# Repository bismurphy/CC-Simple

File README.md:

# CC-Simple
A simple radio using the TI CC-1110 (WORK IN PROGRESS)

License & Legal Information
---------------------------

This project is directly derived from the Planet Labs OpenLST radio. My aim was to simplify it as much as possible to allow for experimentation and education.

The OpenLST is provided under a Creative Commons Attribution-ShareAlike 4.0 International License, which requires me to give them recognition, as well as to also put my work under that license. The Planet Labs repository can be found at https://github.com/OpenLST/openlst-hw

Copyright 2018 Planet Labs Inc. This work is licensed under a
Creative Commons Attribution-ShareAlike 4.0 International License.

This document may contain technology or software the export of which
is or may be restricted by the Export Administration Act and the
Export Administration Regulations (EAR), 15 C.F.R. parts
730-774. Diversion contrary to U.S. law is prohibited.

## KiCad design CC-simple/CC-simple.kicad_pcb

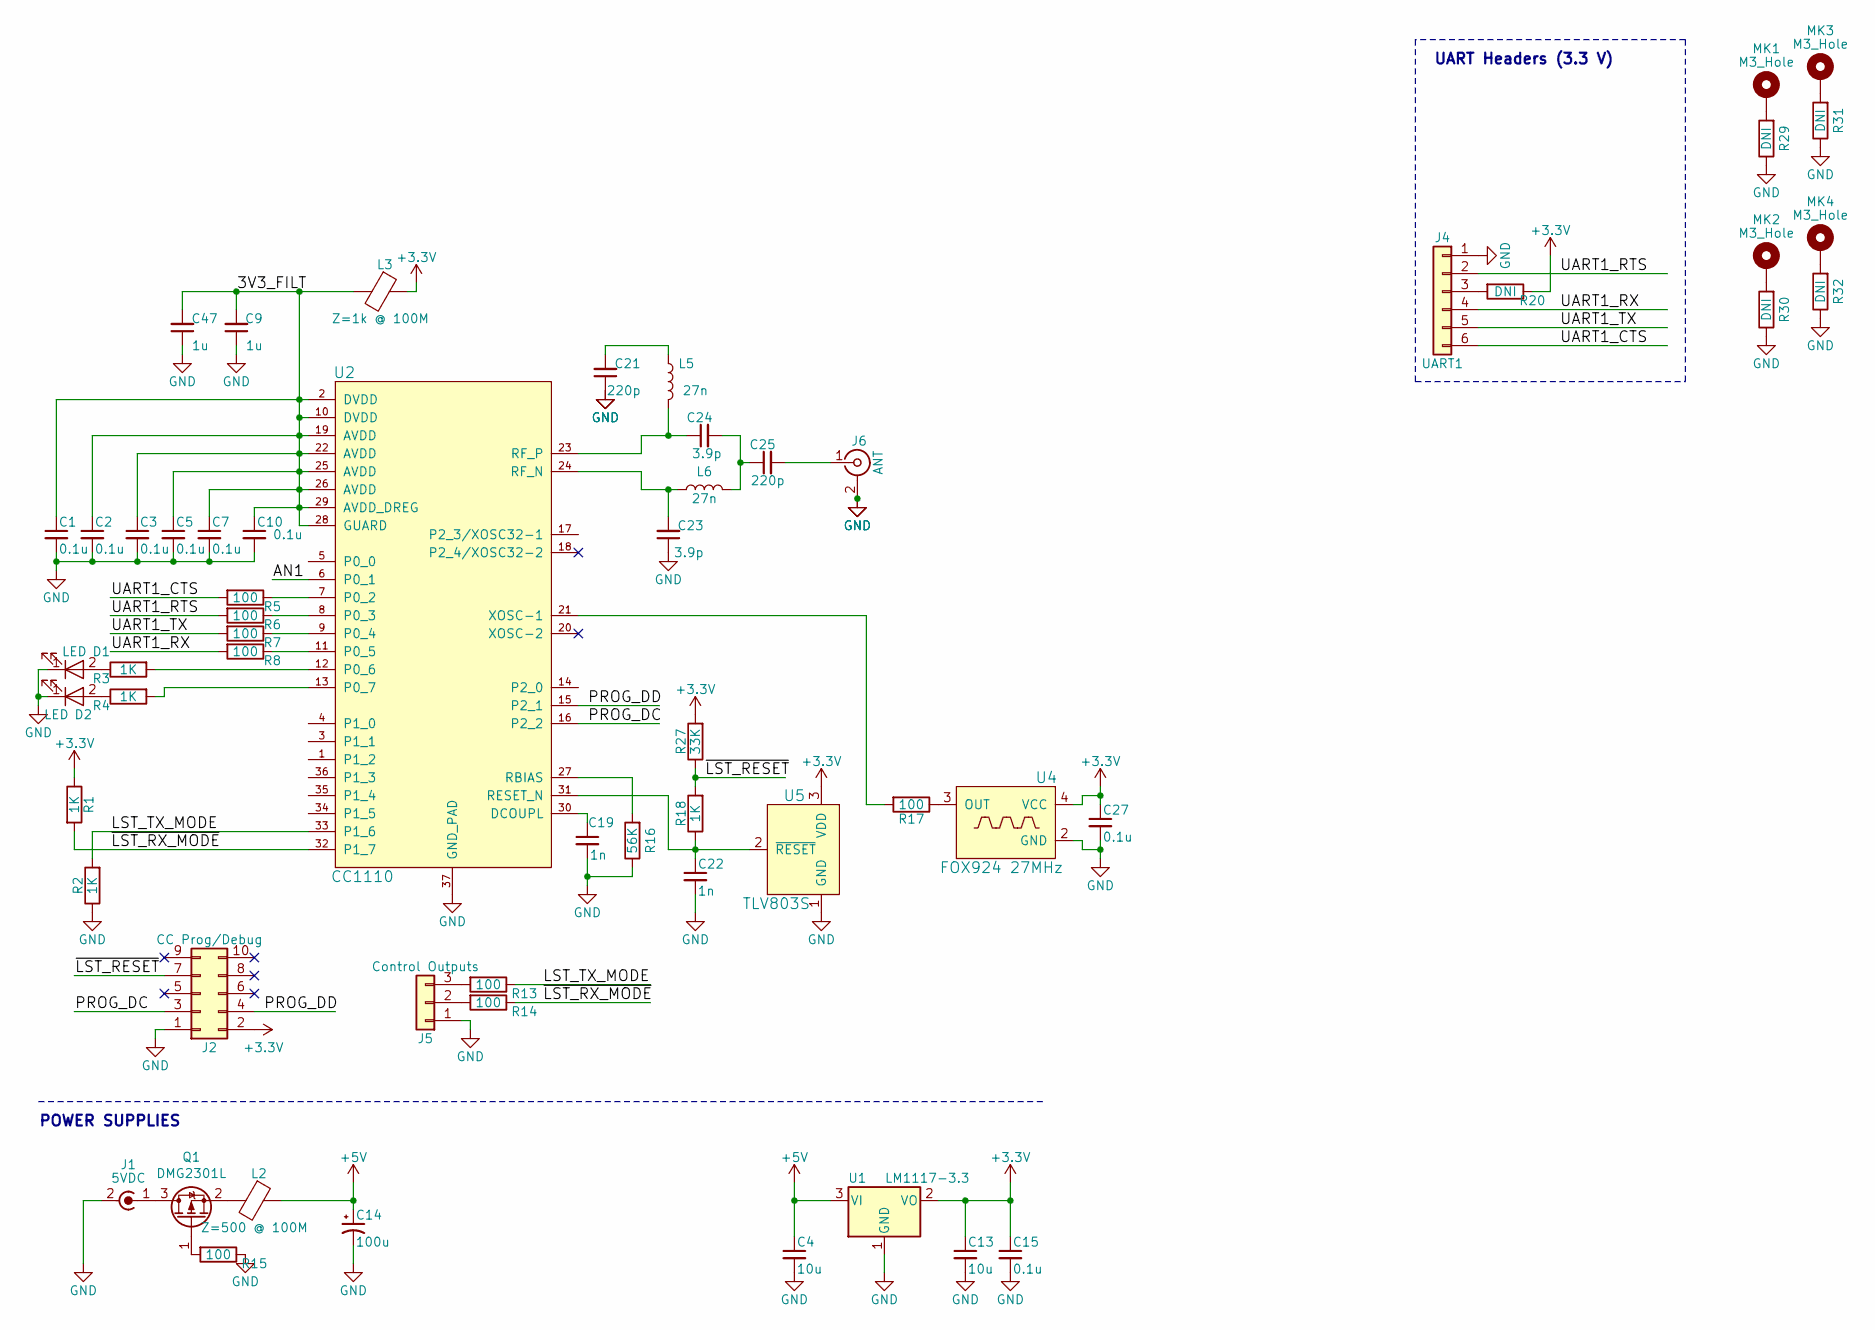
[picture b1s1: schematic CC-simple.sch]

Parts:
C1, C3, C5, C10, C15, C27: 0.1u; C_0603_1608Metric; ManufPN 0603YC104K4T4A
C2, C7: 0.1u; C_0603_1608Metric; ManufPN C0402C221J2GACAUTO
C4, C13: 10u; C_0603_1608Metric; ManufPN GRT188C81A106ME13D
C9, C47: 1u; C_0603_1608Metric; ManufPN CL10B105MO8NNWC
C14: 100u; CP_EIA-3528-15_AVX-H; ManufPN TPSB107M010R0400
C19, C22: 1n; C_0603_1608Metric; ManufPN GCM188R71E102KA37D
C21, C25: 220p; C_0402_1005Metric; ManufPN C0402C221J2GACAUTO
C23, C24: 3.9p; C_0402_1005Metric; ManufPN GJM1555C1H3R9CB01D
D1: LED; LED_0603_1608Metric; ManufPN 150060VS75000
D2: LED; LED_0603_1608Metric; ManufPN 150060SS75000
J1: 5VDC; PinHeader_1x02_P2.54mm_Vertical
J2: CC Prog/Debug; PinHeader_2x05_P1.27mm_Vertical_SMD; ManufPN FTSH-105-01-L-DV-K-P
J4: UART1; PinHeader_1x06_P2.54mm_Vertical; ManufPN 61300611121
J5: Control Outputs; PinHeader_1x03_P2.54mm_Vertical
J6: ANT; SMA_Molex_73251-1153_EdgeMount_Horizontal; ManufPN 732511150
L2: Z=500 @ 100M; L_1206_3216Metric; ManufPN MI1206L501R-10
L3: Z=1k @ 100M; L_0603_1608Metric; ManufPN 74279266
L5, L6: 27n; L_0402_1005Metric; ManufPN LQW15AN27NJ00D
MK1, MK2, MK3, MK4: M3_Hole; MountingHole_3.2mm_M3_Pad_Via
Q1: DMG2301L; SOT-23
R1, R2, R3, R4, R18: 1K; R_0603_1608Metric; ManufPN RC0603JR-071KL
R5, R6, R7, R8, R13, R14, R15, R17: 100; R_0603_1608Metric; ManufPN AC0603FR-07100RL
R16: 56K; R_0603_1608Metric; ManufPN RMCF0603FT56K0
R20, R29, R30, R31, R32: DNI; R_0603_1608Metric
R27: 33K; R_0603_1608Metric; ManufPN AC0603FR-0733KL
U1: LM1117-3.3; SOT-223-3_TabPin2; ManufPN LM1117IMP-3.3/NOPB
U2: CC1110; TI_CC_QFN36; ManufPN CC1110F32RHHR
U4: FOX924 27MHz; Oscillator_SMD_Fordahl_DFAS15-4Pin_5.0x3.2mm; ManufPN FT5HNBPK27.0-T1
U5: TLV803S; SOT-23; ManufPN TLV803SDBZR

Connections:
+3V3: C13.1, C15.1, C27.1, J2.2, L3.1, R1.1, R20.1, R27.2, U1.2 (VO), U4.4 (VCC), U5.3 (VDD)
+5V: C4.1, C14.1, L2.1, U1.3 (VI)
/3V3_FILT: C1.1, C2.1, C3.1, C5.1, C7.1, C9.2, C10.1, C47.2, L3.2, U2.2 (DVDD), U2.10 (DVDD), U2.19 (AVDD), U2.22 (AVDD), U2.25 (AVDD), U2.26 (AVDD), U2.28 (GUARD), U2.29 (AVDD_DREG)
/LST_TX_MODE: R2.2, R13.1, U2.33 (P1_6)
/PROG_DC: J2.3, U2.16 (P2_2)
/PROG_DD: J2.4, U2.15 (P2_1)
/UART1_CTS: J4.6, R5.2
/UART1_RTS: J4.2, R6.2
/UART1_RX: J4.4, R8.2
/UART1_TX: J4.5, R7.2
/~LST_RESET: J2.7, R18.2, R27.1
/~LST_RX_MODE: R1.2, R14.1, U2.32 (P1_7)
GND: C1.2, C2.2, C3.2, C4.2, C5.2, C7.2, C9.1, C10.2, C13.2, C14.2, C15.2, C19.2, C21.1, C22.2, C23.1, C27.2, C47.1, D1.1 (K), D2.1 (K), J1.2 (Ext), J2.1, J4.1, J5.1, J6.2 (Ext), R2.1, R15.1, R16.1, R29.1, R30.1, R31.1, R32.1, U1.1 (GND), U2.37 (GND_PAD), U4.2 (GND), U5.1 (GND)
unnamed: C19.1, U2.30 (DCOUPL)
unnamed: C21.2, L5.1
unnamed: C22.1, R18.1, U2.31 (RESET_N), U5.2 (~RESET~)
unnamed: C23.2, L6.1, U2.24 (RF_N)
unnamed: C24.1, L5.2, U2.23 (RF_P)
unnamed: C24.2, C25.1, L6.2
unnamed: C25.2, J6.1 (In)
unnamed: D1.2 (A), R3.1
unnamed: D2.2 (A), R4.1
unnamed: J1.1 (In), Q1.3 (D)
unnamed: J4.3, R20.2
unnamed: J5.2, R14.2
unnamed: J5.3, R13.2
unnamed: L2.2, Q1.2 (S)
unnamed: MK1.1, R29.2
unnamed: MK2.1, R30.2
unnamed: MK3.1, R31.2
unnamed: MK4.1, R32.2
unnamed: Q1.1 (G), R15.2
unnamed: R3.2, U2.12 (P0_6)
unnamed: R4.2, U2.13 (P0_7)
unnamed: R5.1, U2.7 (P0_2)
unnamed: R6.1, U2.8 (P0_3)
unnamed: R7.1, U2.9 (P0_4)
unnamed: R8.1, U2.11 (P0_5)
unnamed: R16.2, U2.27 (RBIAS)
unnamed: R17.1, U4.3 (OUT)
unnamed: R17.2, U2.21 (XOSC-1)

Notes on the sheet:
POWER SUPPLIES
UART Headers (3.3 V)

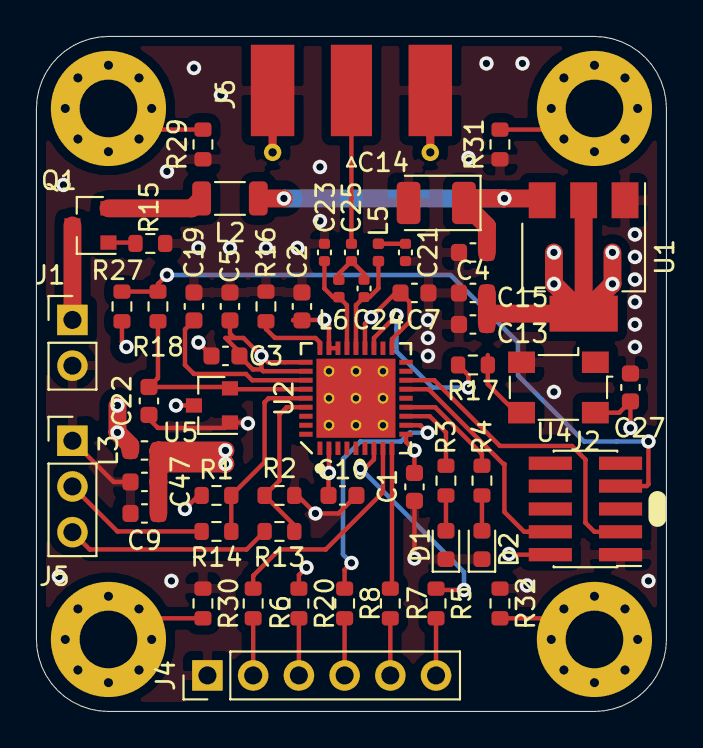
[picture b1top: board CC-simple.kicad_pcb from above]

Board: 4 copper layers, 35.0 x 37.5 mm, 59 parts (0 on the bottom side), 41 nets.

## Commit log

2022-01-14 added openlst attribution to readme
2022-01-16 First board design attempt
